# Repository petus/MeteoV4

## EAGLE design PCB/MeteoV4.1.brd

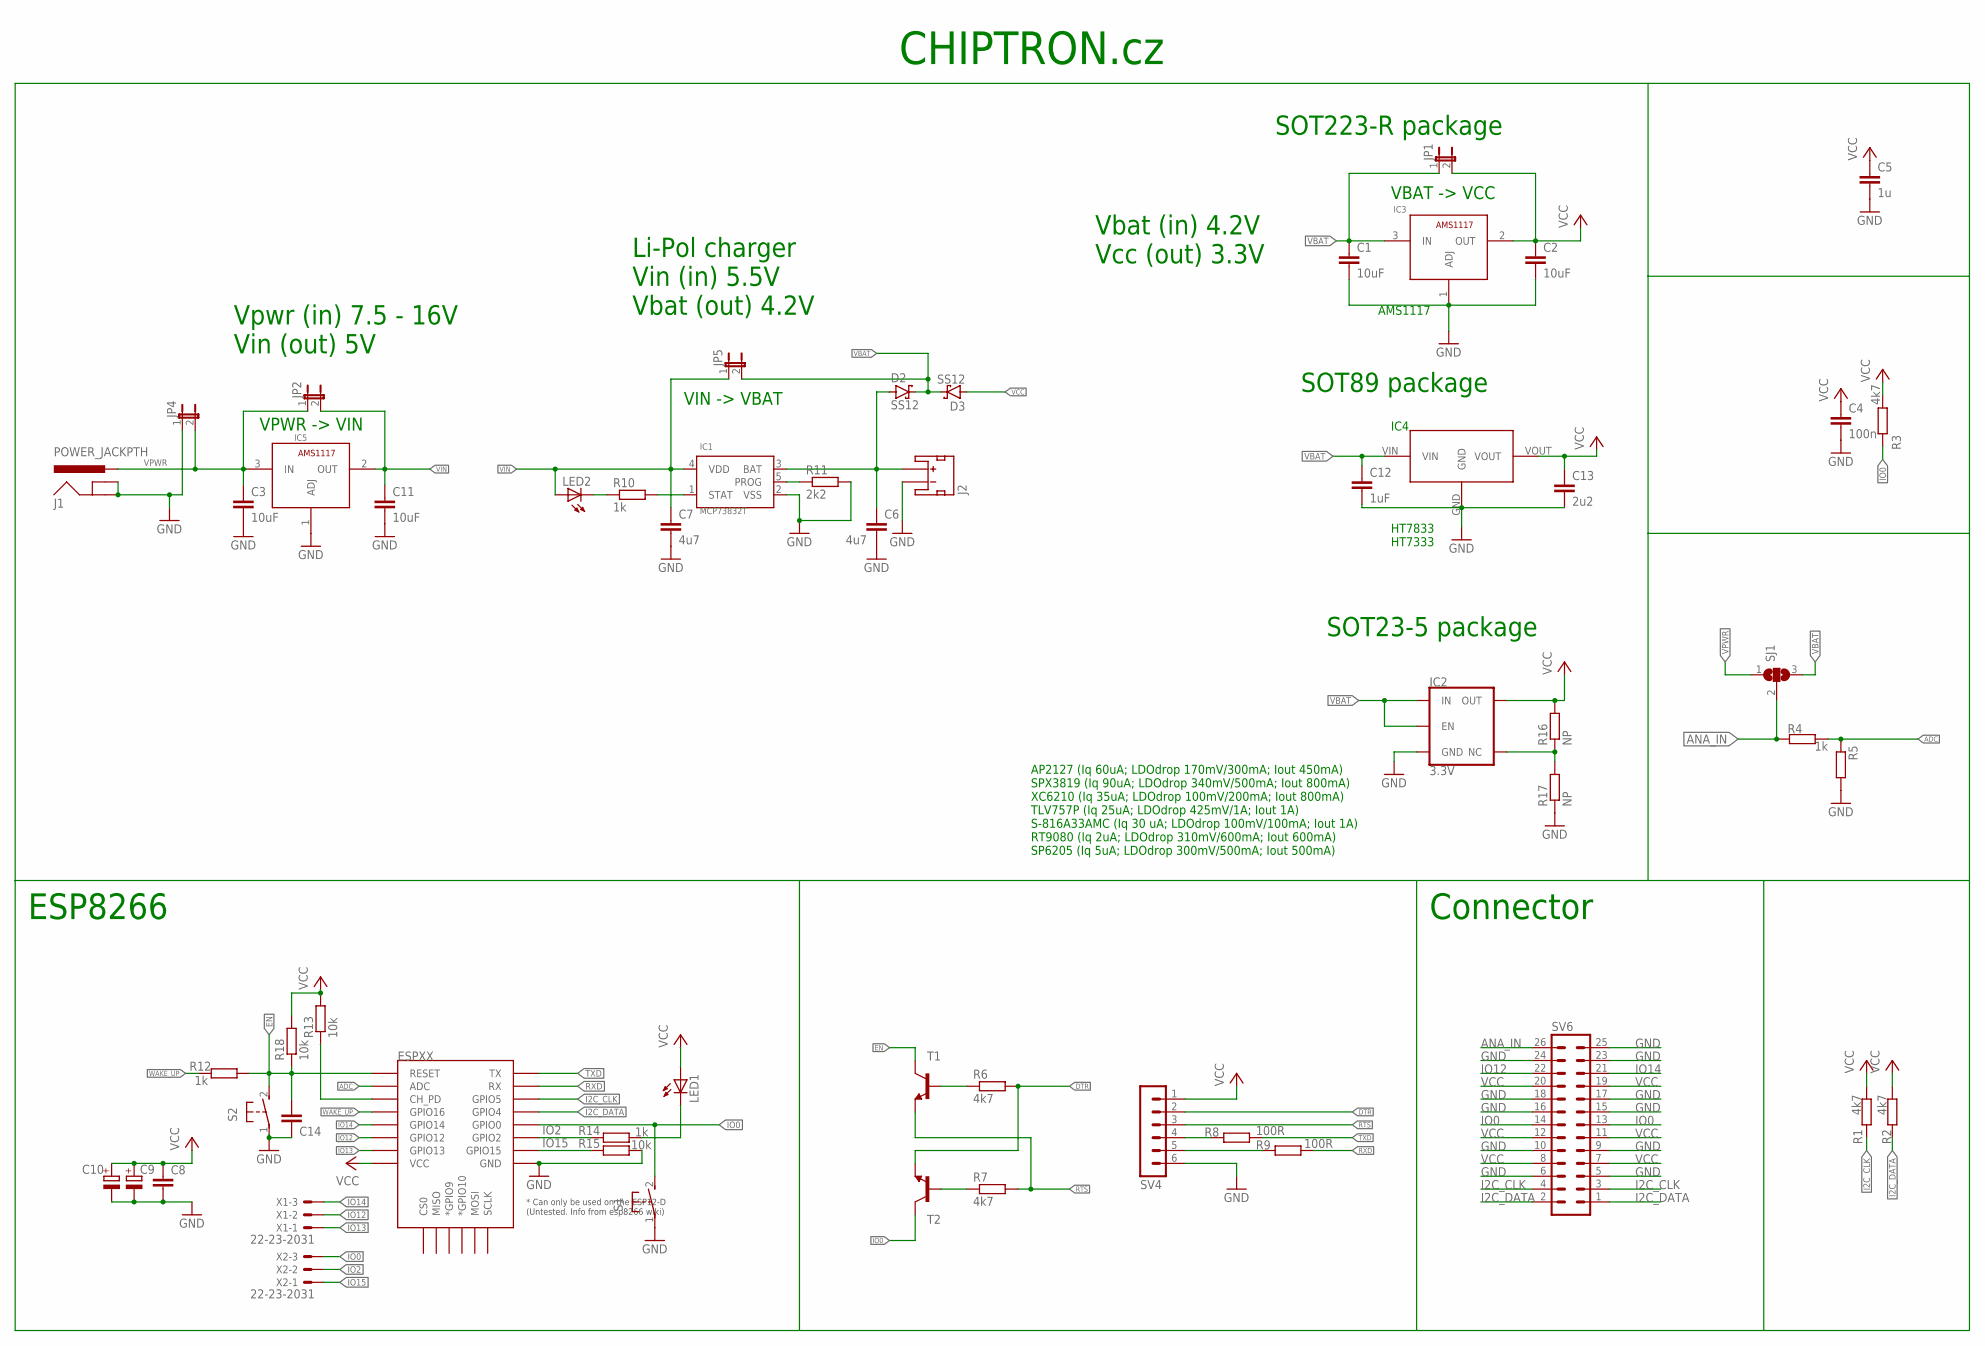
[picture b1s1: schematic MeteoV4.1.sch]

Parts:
C1, C2, C3, C11: 10uF; C0805
C4: 100n; C0805
C5: 1u; C0805
C6, C7: 4u7; C0805
C8, C14: C-EUC0805; C0805
C9: CPOL-EUSMCB; SMC_B
C10: CPOL-EUSMCC; SMC_C
C12: 1uF; C0805
C13: 2u2; C0805
D2, D3: SS12; SMA
ESPXX: ESP12ESMD; ESP12E-SMD
IC1: MCP73832T; SOT23-5
IC2: 3.3V; SOT23-5
IC3, IC5: AMS1117; SOT-223-3
IC4: HT7333; SOT89
J1: POWER_JACKPTH; POWER_JACK_PTH
J2: JST_2MM_MALE; JST-2-SMD
JP1, JP2, JP4, JP5: JP1E; JP1
LED1, LED2: LEDCHIP-LED0805; CHIP-LED0805
R1, R2, R3, R6, R7: 4k7; M0805
R4, R10, R12, R14: 1k; M0805
R5: R-EU_M0805; M0805
R8, R9: 100R; M0805
R11: 2k2; M0805
R13, R15, R18: 10k; M0805
R16, R17: NP; M0805
S1, S2: 31-XX; B3F-31XX
SJ1: SJ2W; SJ_2
SV4: MA06-1
SV6: MA13-2
T1, T2: BC846-NPN-SOT23-BEC; SOT23-BEC
X1, X2: 22-23-2031

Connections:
ADC: ESPXX.ADC, R4.1, R5.1
ANA_IN: R4.2, SJ1.2, SV6.26
DTR: R6.2, SV4.2, T2.E
EN: C14.1, ESPXX.RESET, R12.1, R18.1, S2.2 (S), T1.C
GND: C1.2, C2.2, C3.2, C4.2, C5.2, C6.2, C7.2, C8.2, C9.-, C10.-, C11.2, C12.2, C13.2, C14.2, ESPXX.GND, IC1.2 (VSS), IC2.2 (GND), IC3.1 (ADJ), IC4.GND, IC5.1 (ADJ), J1.GND, J1.GNDBREAK, J2.1 (-), JP4.1, R5.2, R11.2, R15.1, R17.1, S1.1, S2.1, SV4.6, SV6.5, SV6.6, SV6.9, SV6.10, SV6.15, SV6.16, SV6.17, SV6.18, SV6.23, SV6.24, SV6.25
I2C_CLK: ESPXX.GPIO5, R1.1, SV6.3, SV6.4
I2C_DATA: ESPXX.GPIO4, R2.1, SV6.1, SV6.2
IO0: ESPXX.GPIO0, R3.1, S1.2 (S), SV6.13, SV6.14, T2.C, X2.3
IO2: ESPXX.GPIO2, R14.2, X2.2
IO12: ESPXX.GPIO12, SV6.22, X1.2
IO13: ESPXX.GPIO13, X1.1
IO14: ESPXX.GPIO14, SV6.21, X1.3
IO15: ESPXX.GPIO15, R15.2, X2.1
unnamed: R7.1, T2.B
unnamed: R8.1, SV4.4
unnamed: R9.1, SV4.5
unnamed: IC1.5 (PROG), R11.1
unnamed: ESPXX.CH_PD, R13.1
unnamed: LED1.C, R14.1
unnamed: IC2.4 (NC), R16.1, R17.2
unnamed: R6.1, T1.B
unnamed: IC1.1 (STAT), R10.2
unnamed: LED2.C, R10.1
unnamed: C6.1, D2.A, IC1.3 (BAT), J2.2 (+)
RTS: R7.2, SV4.3, T1.E
RXD: ESPXX.RXD0 (RX), R9.2
TXD: ESPXX.TXD0 (TX), R8.2
VBAT: C1.1, C12.1, D2.C, D3.C, IC2.1 (IN), IC2.3 (EN), IC3.3 (IN), IC4.VIN, JP1.1, JP5.2, SJ1.3
VCC: C2.1, C4.1, C5.1, C8.1, C9.+, C10.+, C13.1, D3.A, ESPXX.VCC, IC2.5 (OUT), IC3.2 (OUT), IC4.VOUT, JP1.2, LED1.A, R1.2, R2.2, R3.2, R13.2, R16.2, R18.2, SV4.1, SV6.7, SV6.8, SV6.11, SV6.12, SV6.19, SV6.20
VIN: C7.1, C11.1, IC1.4 (VDD), IC5.2 (OUT), JP2.2, JP5.1, LED2.A
VPWR: C3.1, IC5.3 (IN), J1.PWR, JP2.1, JP4.2, SJ1.1
WAKE_UP: ESPXX.GPIO16, R12.2

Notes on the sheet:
CHIPTRON.cz
AP2127 (Iq 60uA; LDOdrop 170mV/300mA; Iout 450mA) SPX3819 (Iq 90uA; LDOdrop 340mV/500mA; Iout 800mA) XC6210 (Iq 35uA; LDOdrop 100mV/200mA; Iout 800mA) TLV757P (Iq 25uA; LDOdrop 425mV/1A; Iout 1A) S-816A33AMC (Iq 30 uA; LDOdrop 100mV/100mA; Iout 1A) RT9080 (Iq 2uA; LDOdrop 310mV/600mA; Iout 600mA) S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
Vpwr (in) 7.5 - 16V Vin (out) 5V
Li-Pol charger Vin (in) 5.5V Vbat (out) 4.2V
SOT89 package
SOT223-R package
SOT23-5 package
Vbat (in) 4.2V Vcc (out) 3.3V
ESP8266
Connector
VPWR -> VIN
VIN -> VBAT
VBAT -> VCC
AMS1117
HT7833 HT7333
IC4

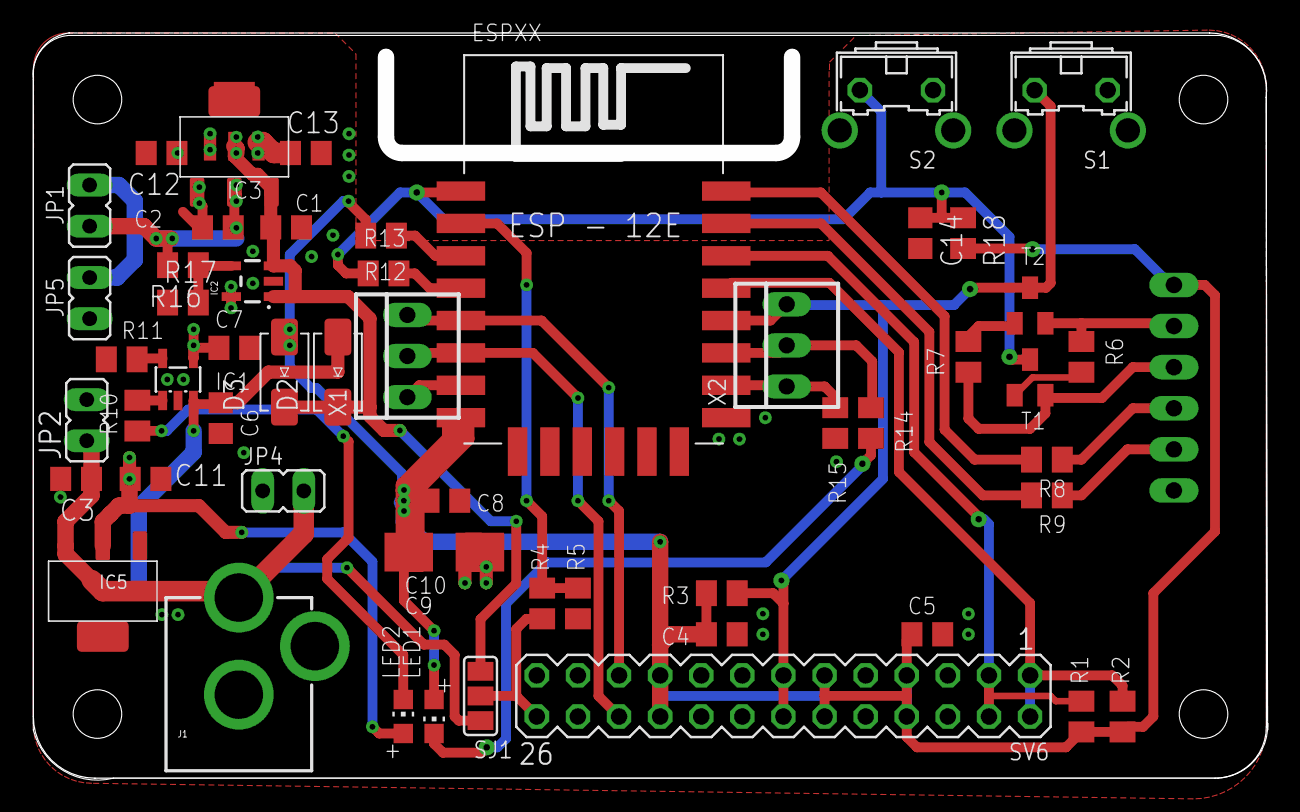
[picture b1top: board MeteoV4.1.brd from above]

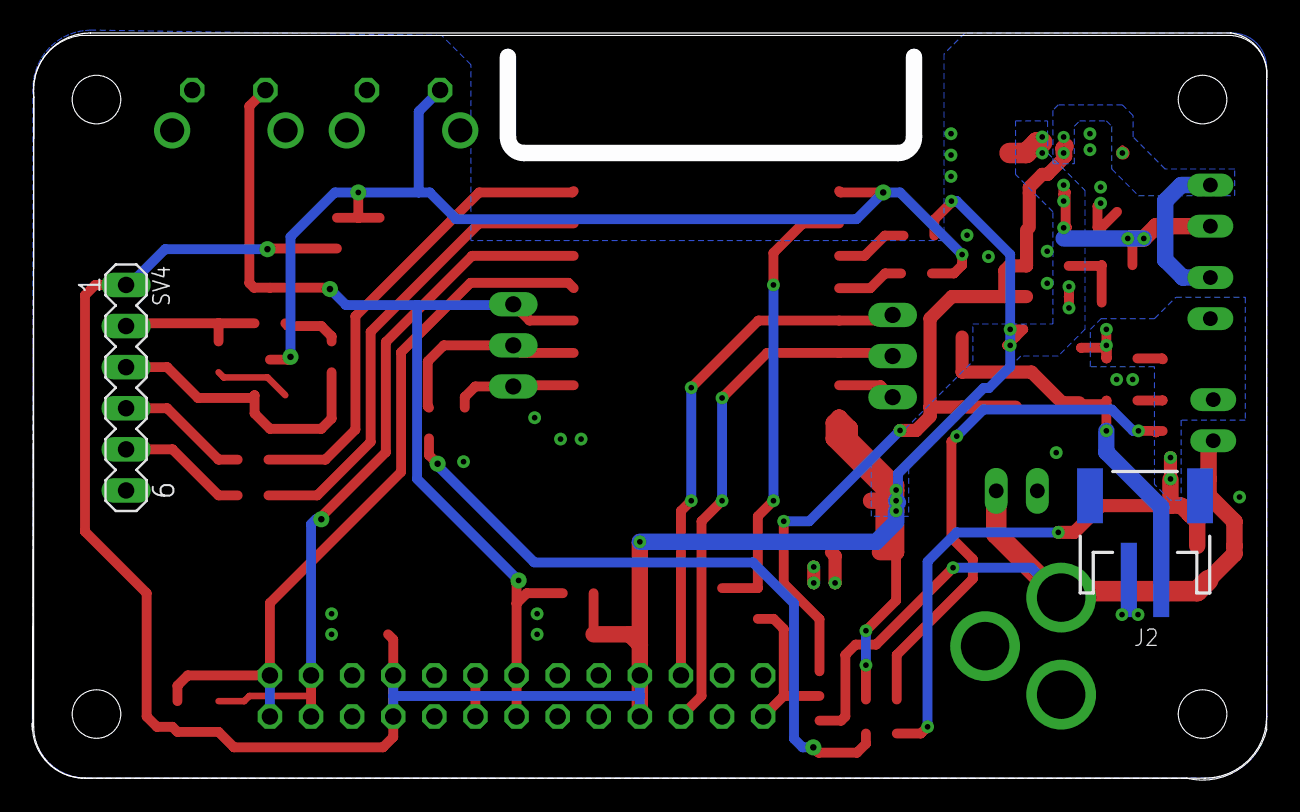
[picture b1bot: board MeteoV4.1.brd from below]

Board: 2 copper layers, 75.3 x 45.2 mm, 57 parts (2 on the bottom side), 32 nets.

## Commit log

2020-10-08 Create TODO
2020-10-08 Update TODO

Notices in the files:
parts and their libraries:
SparkFun: Licensing: CC v3.0 Share-Alike You are welcome to use this library for commercial purposes.
SparkFun-connectors: Licensing: Creative Commons ShareAlike 4.0 International - https://creativecommons.org/licenses/by-sa/4.0
